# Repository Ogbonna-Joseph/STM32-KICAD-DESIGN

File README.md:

# STM32-KICAD-DESIGN
DESIGN PCB
..
...
..

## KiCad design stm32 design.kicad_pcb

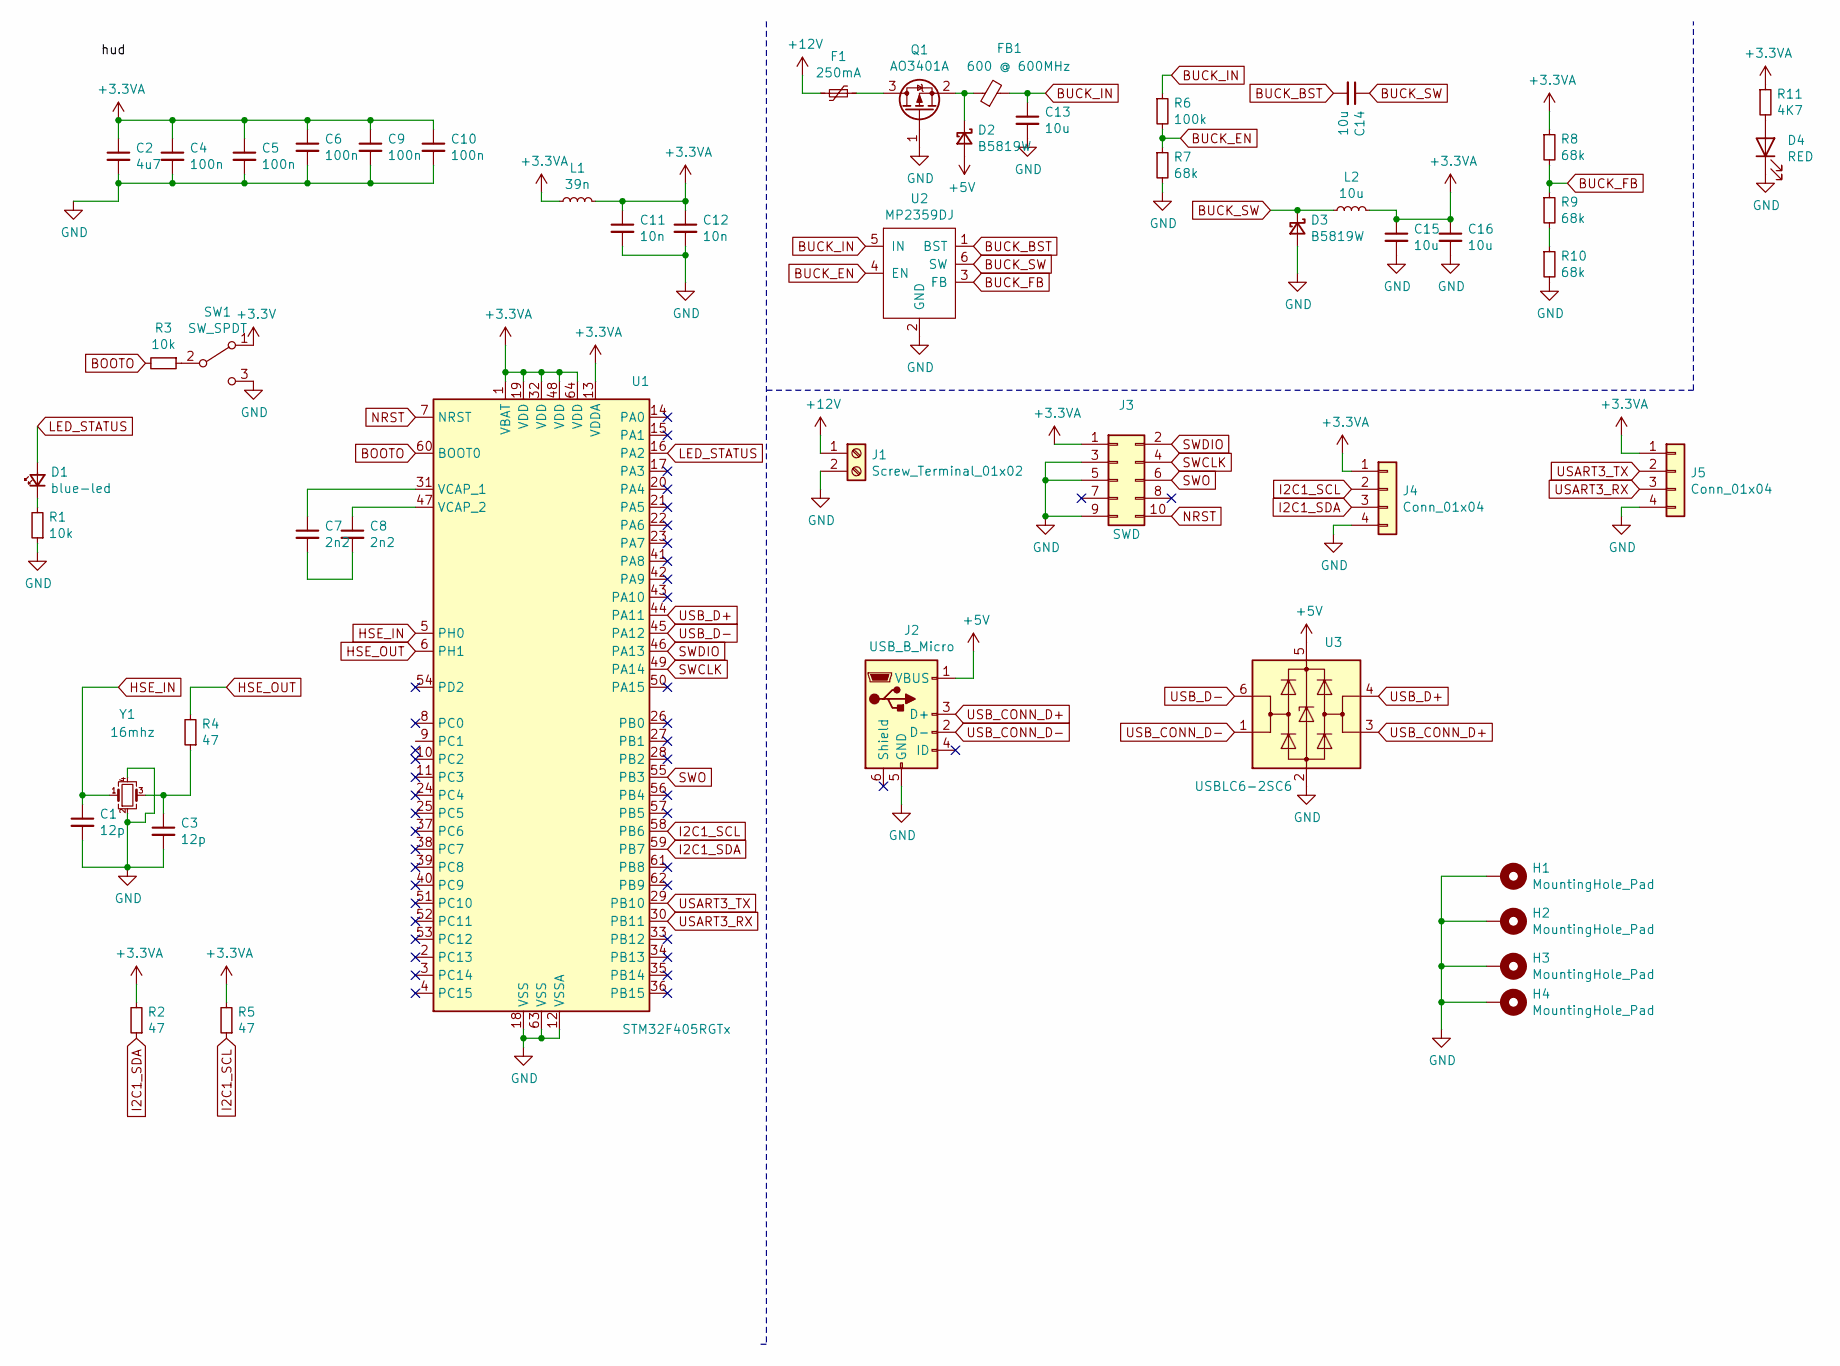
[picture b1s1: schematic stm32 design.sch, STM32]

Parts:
C1, C3: 12p; C_0402_1005Metric
C2: 4u7; C_0603_1608Metric
C4, C5, C6, C9, C10: 100n; C_0402_1005Metric
C7, C8: 2n2; C_0603_1608Metric
C11: 10n; C_0402_1005Metric
C12: 10n; C_0603_1608Metric
C13, C14, C15, C16: 10u; C_1206_3216Metric
D1: blue-led; LED_0603_1608Metric
D2, D3: B5819W; D_SOD-123
D4: RED; LED_0603_1608Metric
F1: 250mA; Fuse_1206_3216Metric
FB1: 600 @ 600MHz; L_0805_2012Metric
H1, H2, H3, H4: MountingHole_Pad; MountingHole_2.2mm_M2_Pad_Via
J1: Screw_Terminal_01x02; TerminalBlock_Phoenix_PT-1,5-2-3.5-H_1x02_P3.50mm_Horizontal
J2: USB_B_Micro; USB_Micro-AB_Molex_47590-0001
J3: SWD; PinSocket_2x05_P1.00mm_Vertical_SMD
J4, J5: Conn_01x04; Molex_PicoBlade_53048-0410_1x04_P1.25mm_Horizontal
L1: 39n; L_0402_1005Metric
L2: 10u; L_Sunlord_MWSA0518_5.4x5.2mm
Q1: AO3401A; SOT-23
R1, R3: 10k; R_0603_1608Metric
R2, R4, R5: 47; R_0402_1005Metric
R6: 100k; R_0603_1608Metric
R7, R8, R9, R10: 68k; R_0603_1608Metric
R11: 4K7; R_0603_1608Metric
SW1: SW_SPDT; SW_SPDT_PCM12
U1: STM32F405RGTx; LQFP-64_10x10mm_P0.5mm
U2: MP2359DJ; SOT-23-6
U3: USBLC6-2SC6; SOT-23-6
Y1: 16mhz; Crystal_SMD_3225-4Pin_3.2x2.5mm

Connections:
+3.3VA: C2.1, C4.1, C5.1, C6.1, C9.1, C10.1, C11.1, C12.1, C15.1, C16.1, J3.1, J4.1, J5.1, L1.1, L1.2, L2.2, R2.2, R5.2, R8.1, R11.1, U1.1 (VBAT), U1.13 (VDDA), U1.19 (VDD), U1.32 (VDD), U1.48 (VDD), U1.64 (VDD)
+3V3: SW1.1 (A)
+5V: D2.2 (A), J2.1 (VBUS), U3.5 (VBUS)
+12V: F1.2, J1.1
BOOTO: R3.2, U1.60 (BOOT0)
BUCK_BST: C14.2, U2.1 (BST)
BUCK_EN: R6.2, R7.1, U2.4 (EN)
BUCK_FB: R8.2, R9.1, U2.3 (FB)
BUCK_IN: C13.1, FB1.2, R6.1, U2.5 (IN)
BUCK_SW: C14.1, D3.1 (K), L2.1, U2.6 (SW)
GND: C1.2, C2.2, C3.2, C4.2, C5.2, C6.2, C9.2, C10.2, C11.2, C12.2, C13.2, C15.2, C16.2, D3.2 (A), D4.1 (K), H1.1, H2.1, H3.1, H4.1, J1.2, J2.5 (GND), J3.3, J3.5, J3.9, J4.4, J5.4, Q1.1 (G), R1.1, R7.2, R10.2, SW1.3 (C), U1.12 (VSSA), U1.18 (VSS), U1.63 (VSS), U2.2 (GND), U3.2 (GND), Y1.2, Y1.4
HSE_IN: C1.1, U1.5 (PH0), Y1.1
HSE_OUT: R4.2, U1.6 (PH1)
I2C1_SCL: J4.2, R5.1, U1.58 (PB6)
I2C1_SDA: J4.3, R2.1, U1.59 (PB7)
LED_STATUS: D1.2 (A), U1.16 (PA2)
NRST: J3.10, U1.7 (NRST)
unnamed: C3.1, R4.1, Y1.3
unnamed: C7.1, U1.31 (VCAP_1)
unnamed: C7.2, C8.2
unnamed: C8.1, U1.47 (VCAP_2)
unnamed: D1.1 (K), R1.2
unnamed: D2.1 (K), FB1.1, Q1.2 (S)
unnamed: D4.2 (A), R11.2
unnamed: F1.1, Q1.3 (D)
unnamed: R3.1, SW1.2 (B)
unnamed: R9.2, R10.1
SWCLK: J3.4, U1.49 (PA14)
SWDIO: J3.2, U1.46 (PA13)
SWO: J3.6, U1.55 (PB3)
USART3_RX: J5.3, U1.30 (PB11)
USART3_TX: J5.2, U1.29 (PB10)
USB_CONN_D+: J2.3 (D+), U3.3 (I/O2)
USB_CONN_D-: J2.2 (D-), U3.1 (I/O1)
USB_D+: U1.44 (PA11), U3.4 (I/O2)
USB_D-: U1.45 (PA12), U3.6 (I/O1)

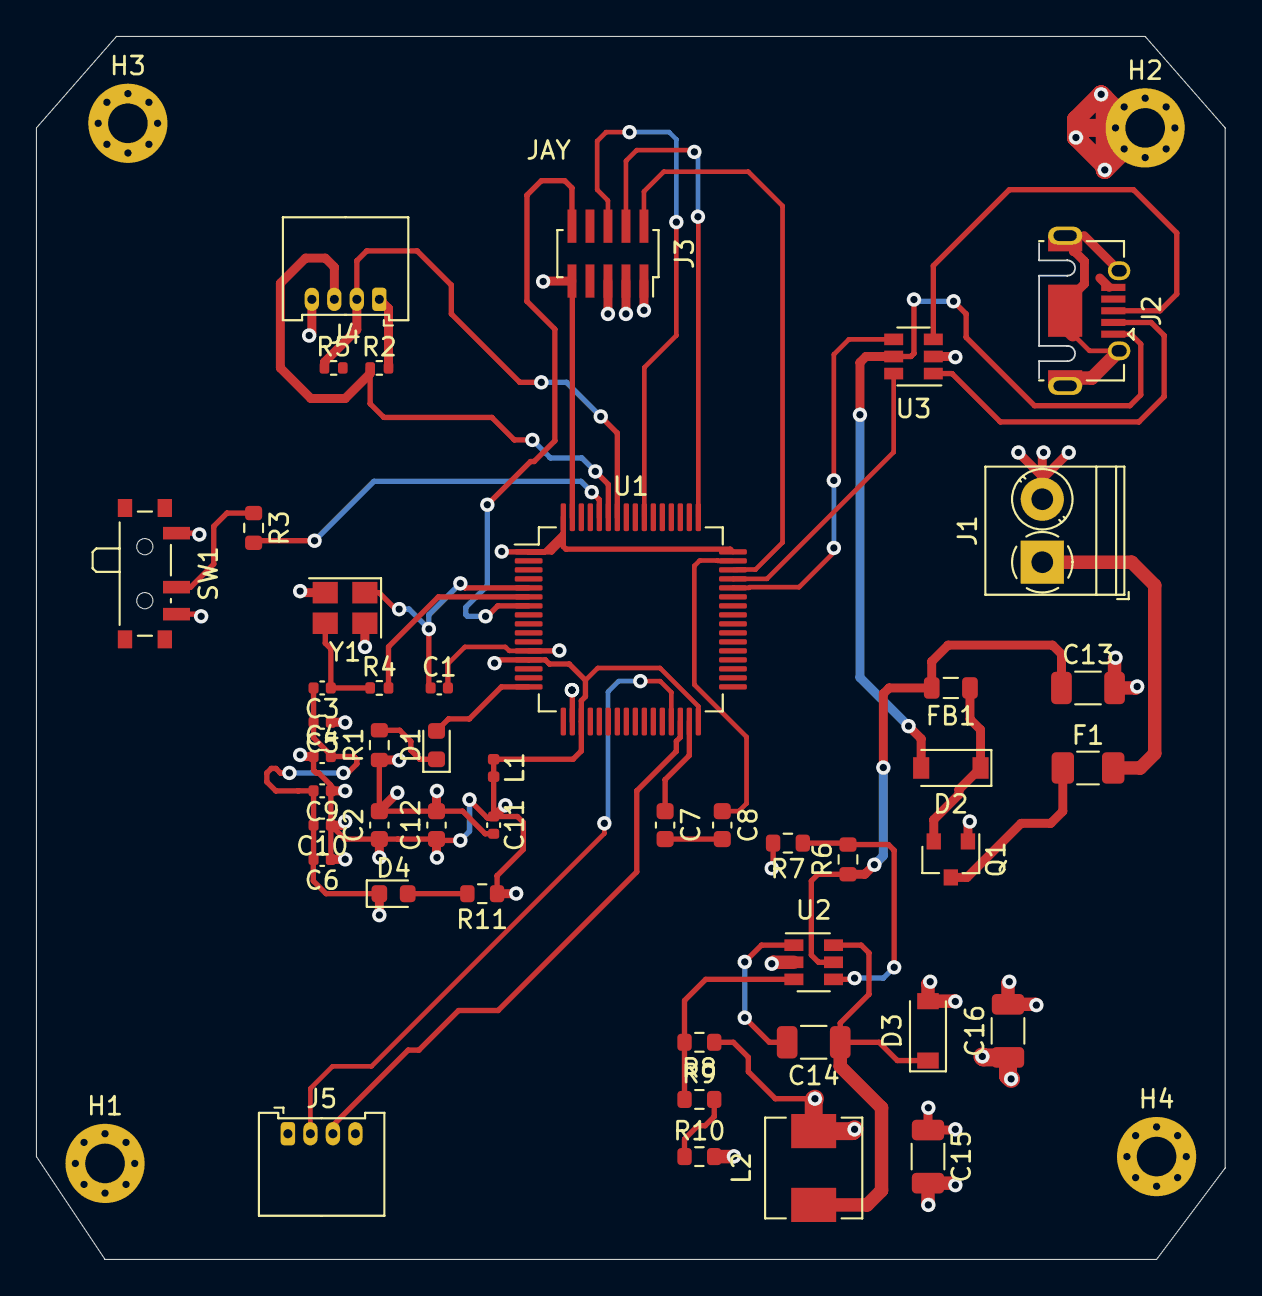
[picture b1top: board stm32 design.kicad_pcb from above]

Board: 4 copper layers, 66.0 x 67.9 mm, 50 parts (0 on the bottom side), 35 nets.

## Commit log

2021-05-08 stm32 deign
